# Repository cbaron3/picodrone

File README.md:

# picodrone

Micro drone project using STM32

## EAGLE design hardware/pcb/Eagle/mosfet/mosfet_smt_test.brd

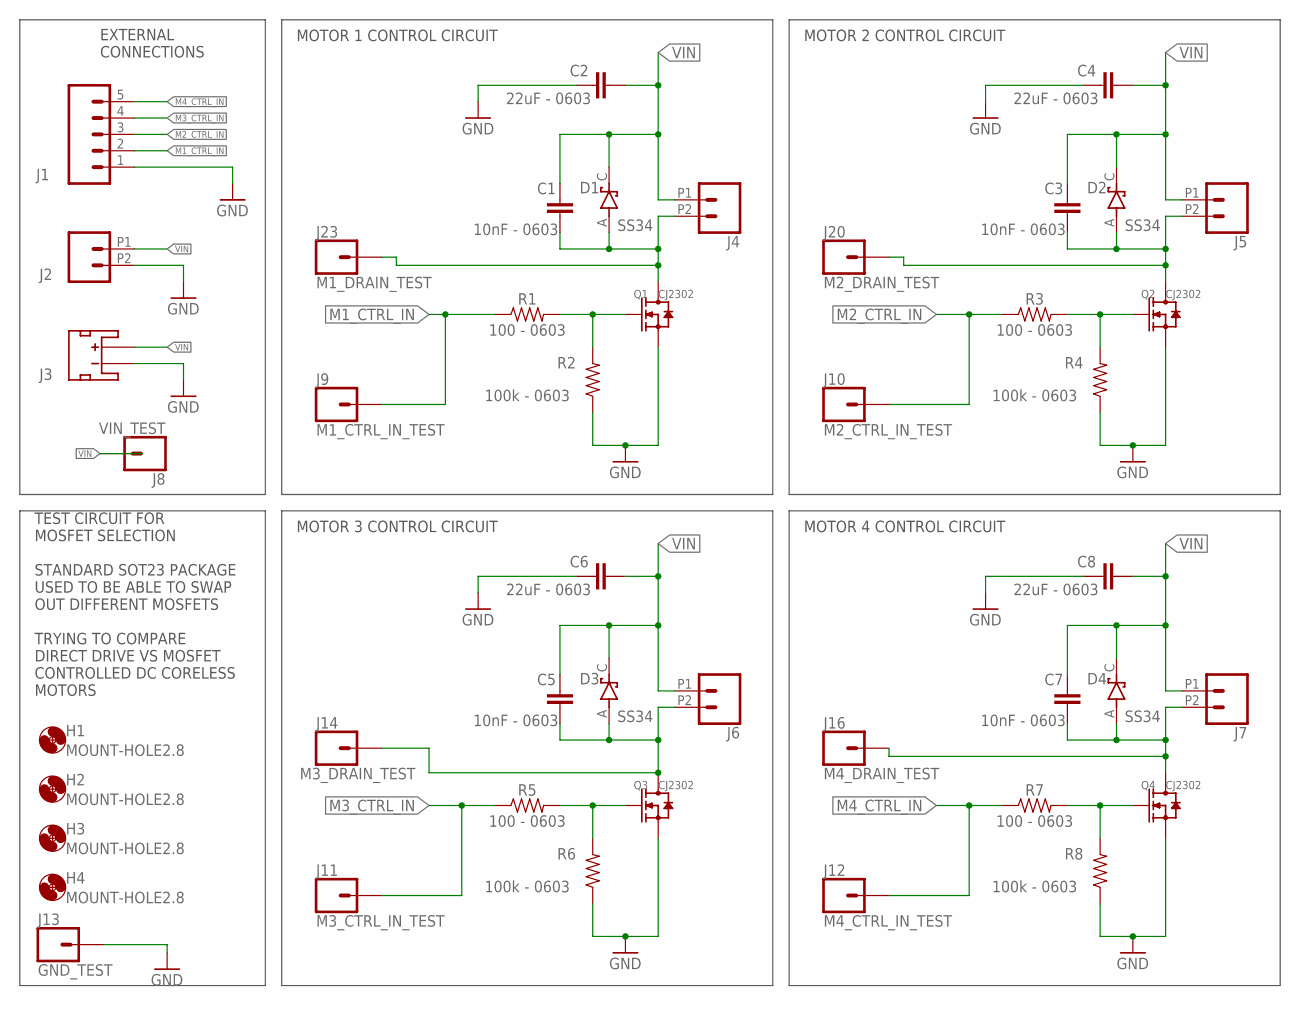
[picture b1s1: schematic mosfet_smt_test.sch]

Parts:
C1, C3, C5, C7: 10nF - 0603; CAP_0603
C2, C4, C6, C8: 22uF - 0603; CAP_0603
D1, D2, D3, D4: SS34; DIOM7959X265N
H1, H2, H3, H4: MOUNT-HOLE2.8; 2,8
J1: CONN_05; 1X05
J2, J4, J5, J6, J7: CONN_022.54MM_SCREWTERM; 1X02_2.54_SCREWTERM
J3: JST_2MM_MALE; JST-2-SMD
J8: VIN_TEST; 1X01
J9: M1_CTRL_IN_TEST; 1X01
J10: M2_CTRL_IN_TEST; 1X01
J11: M3_CTRL_IN_TEST; 1X01
J12: M4_CTRL_IN_TEST; 1X01
J13: GND_TEST; 1X01
J14: M3_DRAIN_TEST; 1X01
J16: M4_DRAIN_TEST; 1X01
J20: M2_DRAIN_TEST; 1X01
J23: M1_DRAIN_TEST; 1X01
Q1, Q2, Q3, Q4: CJ2302; SOT-23
R1, R3, R5, R7: 100 - 0603; 0603
R2, R4, R6, R8: 100k - 0603; 0603

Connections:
GND: C2.2, C4.2, C6.2, C8.2, J1.1, J2.P2 (2), J3.1 (-), J13.1, Q1.2 (S), Q2.2 (S), Q3.2 (S), Q4.2 (S), R2.1, R4.1, R6.1, R8.1
M1_CTRL_IN: J1.2, J9.1, R1.1
M2_CTRL_IN: J1.3, J10.1, R3.1
M3_CTRL_IN: J1.4, J11.1, R5.1
M4_CTRL_IN: J1.5, J12.1, R7.1
unnamed: Q1.1 (G), R1.2, R2.2
unnamed: C1.2, D1.A, J4.P2 (2), J23.1, Q1.3 (D)
unnamed: Q2.1 (G), R3.2, R4.2
unnamed: C3.2, D2.A, J5.P2 (2), J20.1, Q2.3 (D)
unnamed: Q3.1 (G), R5.2, R6.2
unnamed: C5.2, D3.A, J6.P2 (2), J14.1, Q3.3 (D)
unnamed: Q4.1 (G), R7.2, R8.2
unnamed: C7.2, D4.A, J7.P2 (2), J16.1, Q4.3 (D)
VIN: C1.1, C2.1, C3.1, C4.1, C5.1, C6.1, C7.1, C8.1, D1.C (K), D2.C (K), D3.C (K), D4.C (K), J2.P1 (1), J3.2 (+), J4.P1 (1), J5.P1 (1), J6.P1 (1), J7.P1 (1), J8.1

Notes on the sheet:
MOTOR 1 CONTROL CIRCUIT
MOTOR 2 CONTROL CIRCUIT
MOTOR 3 CONTROL CIRCUIT
MOTOR 4 CONTROL CIRCUIT
EXTERNAL CONNECTIONS
TEST CIRCUIT FOR MOSFET SELECTION STANDARD SOT23 PACKAGE USED TO BE ABLE TO SWAP OUT DIFFERENT MOSFETS TRYING TO COMPARE DIRECT DRIVE VS MOSFET CONTROLLED DC CORELESS MOTORS

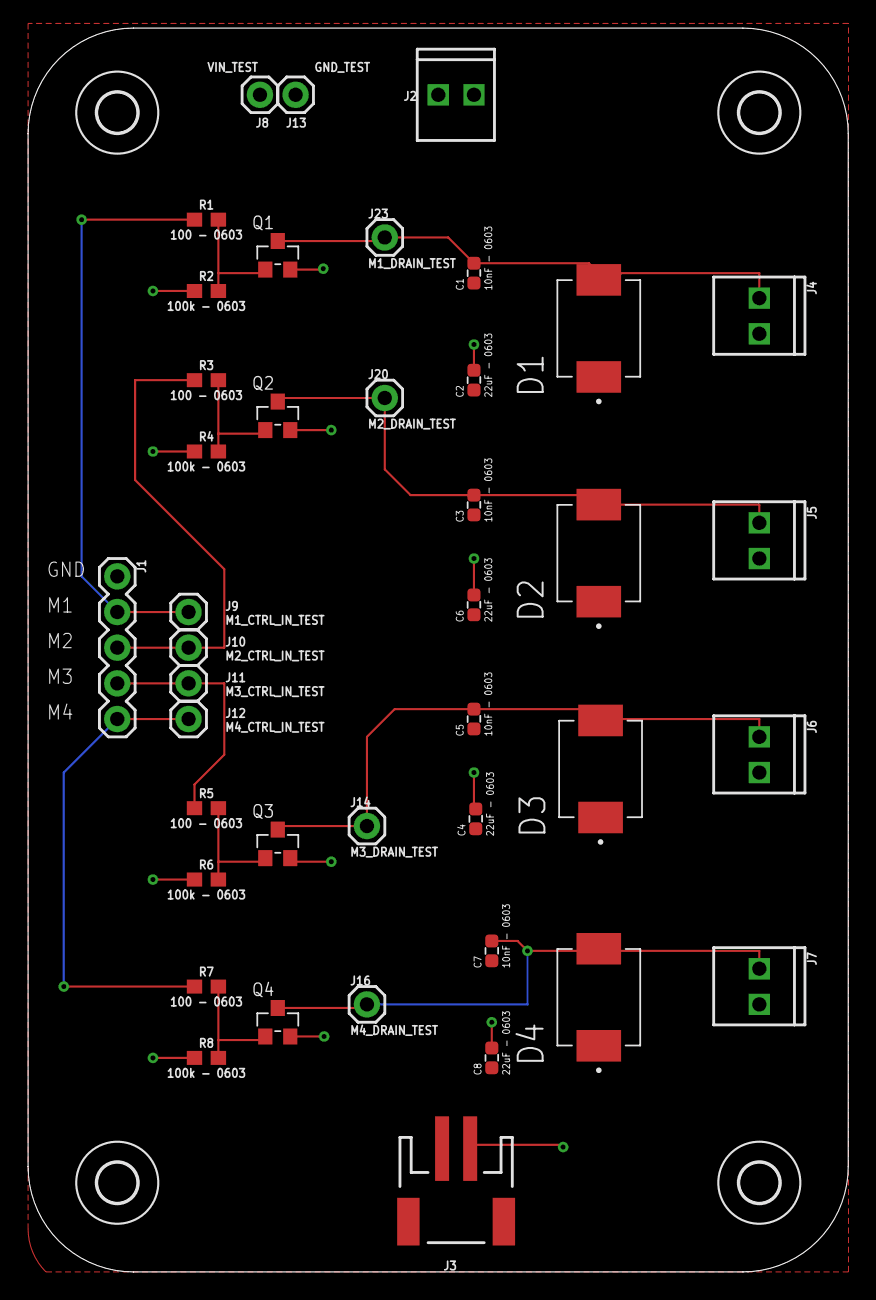
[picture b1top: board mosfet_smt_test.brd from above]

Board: 2 copper layers, 58.4 x 88.6 mm, 45 parts (0 on the bottom side), 14 nets.

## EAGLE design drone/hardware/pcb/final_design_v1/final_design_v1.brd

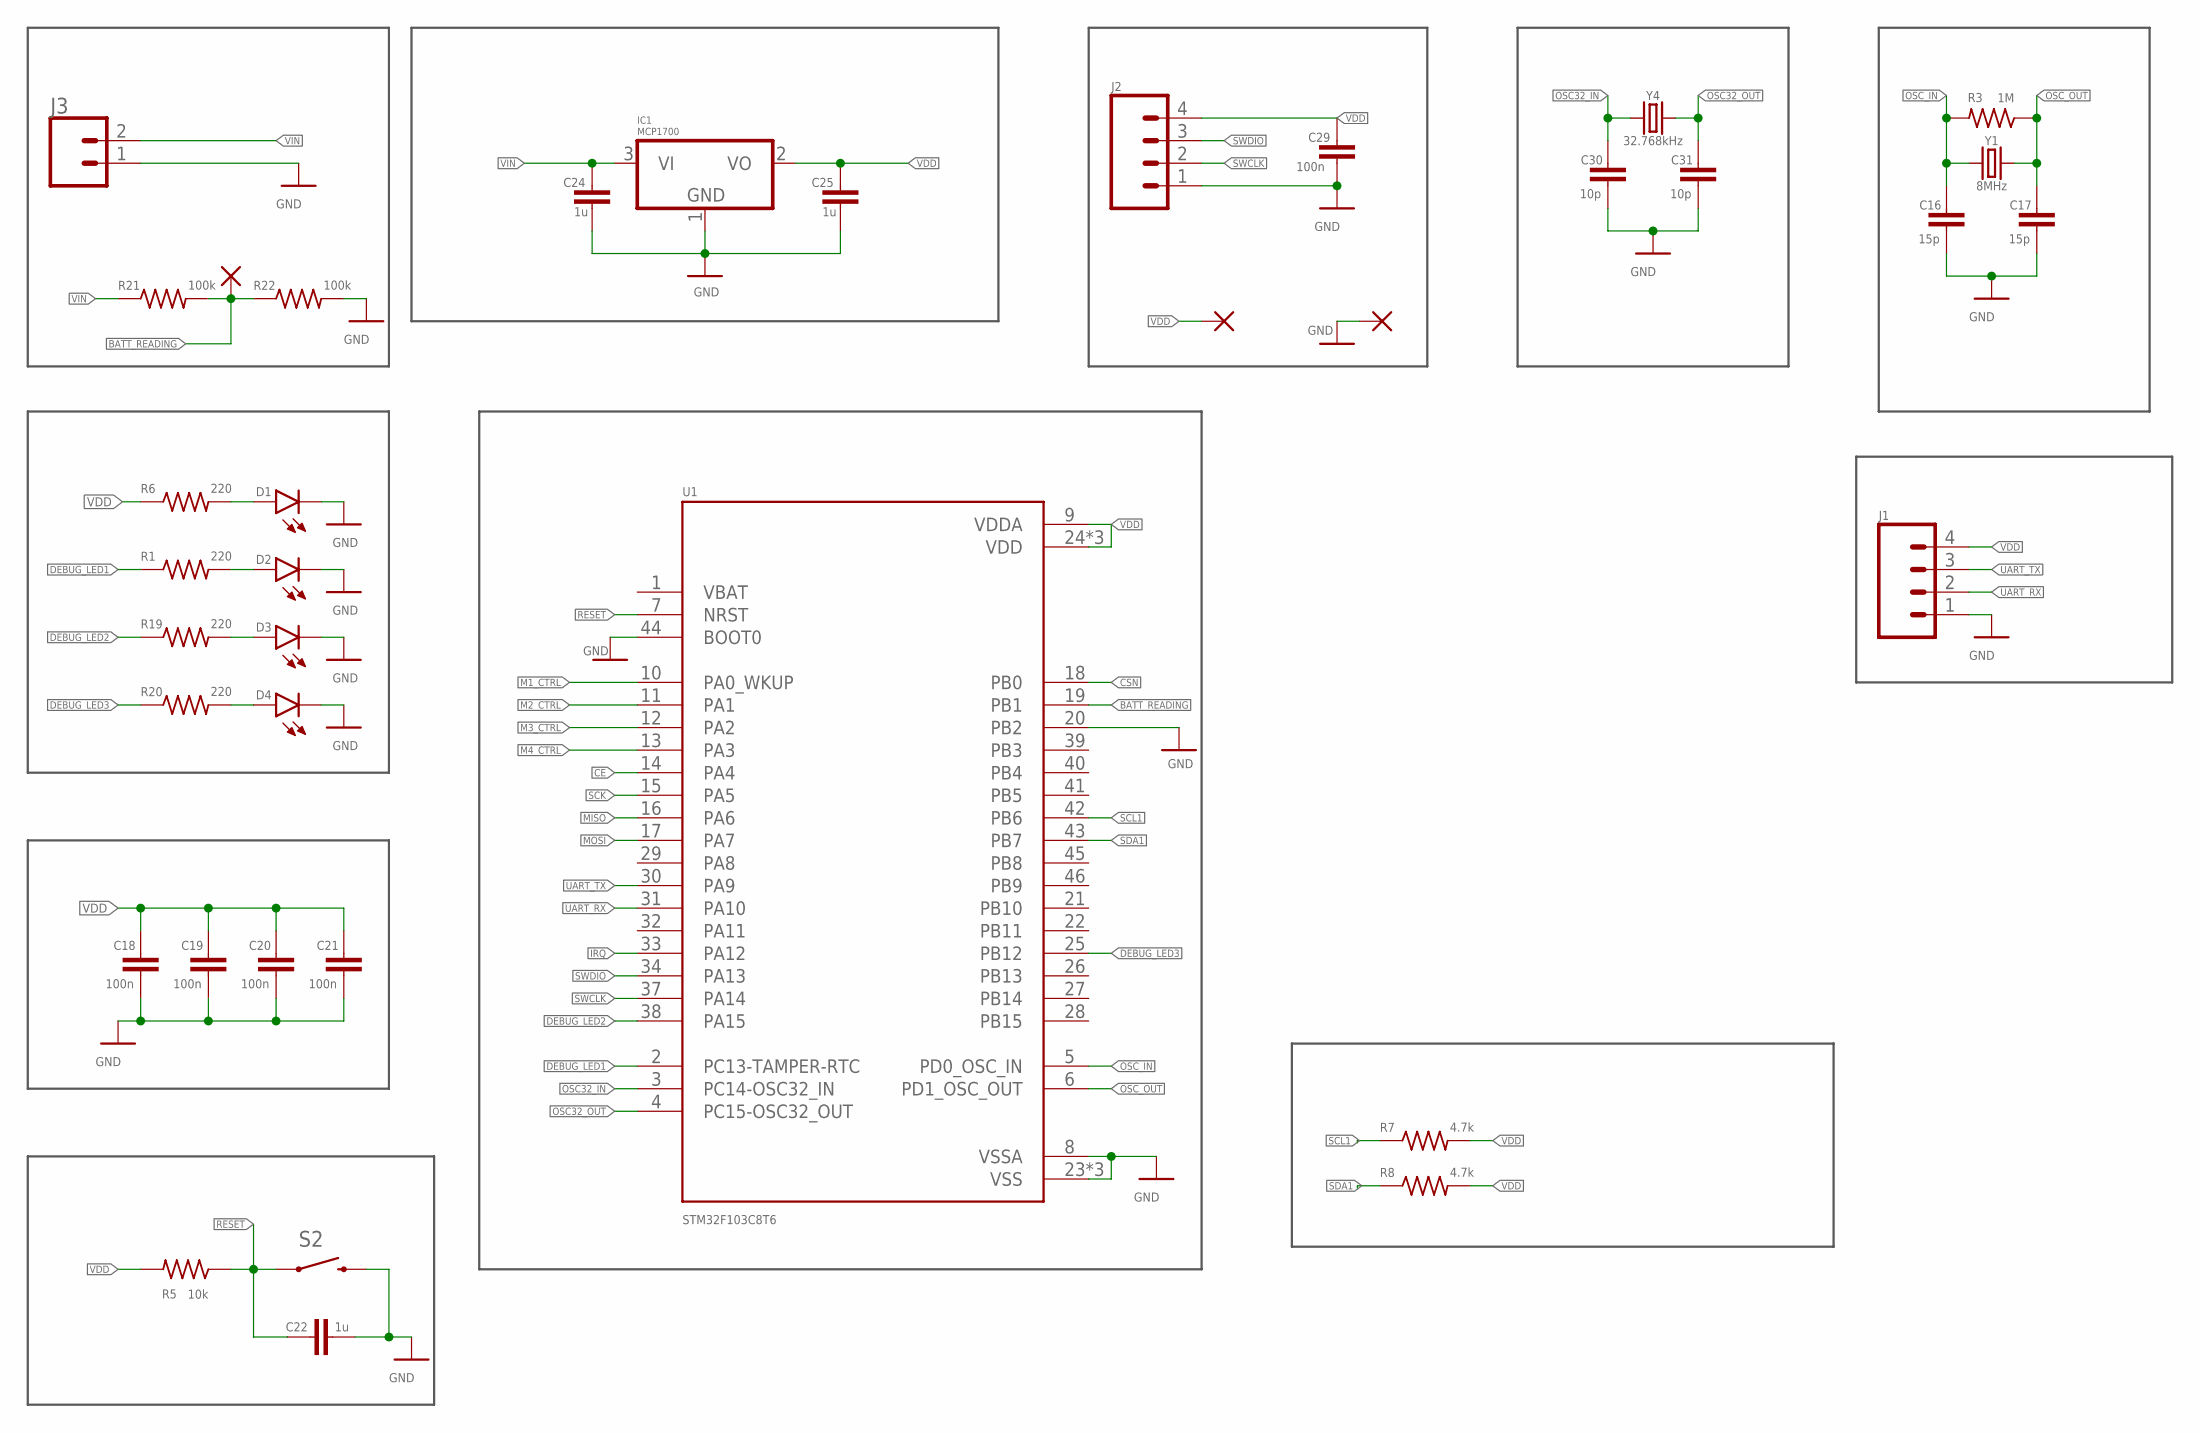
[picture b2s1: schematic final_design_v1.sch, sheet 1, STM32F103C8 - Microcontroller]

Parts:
+M18, +M19, +M20: SMD2; SMD1,27-2,54
C16, C17: 15p; CAP_0603
C18, C19, C20, C21, C29: 100n; CAP_0603
C22, C24, C25: 1u; CAP_0603
C30, C31: 10p; CAP_0603
D1, D2, D3, D4: LED0603; LED-0603
IC1: MCP1700; SOT23
J1, J2: CONN_04; 1X04
J3: CONN_02; 1X02
R1, R6, R19, R20: 220; RES_0603
R3: 1M; RES_0603
R5: 10k; RES_0603
R7, R8: 4.7k; RES_0603
R21, R22: 100k; RES_0603
S2: RS032G05A3SM-SPST-MOMENTARY-SWSMD-1101NE; TACTILE-SWITCH-1101NE
U1: STM32F103C8T6; QFP50P900X900X160-48N
Y1: 8MHz; CRYSTAL-SMD-5X3.2-4PAD
Y4: 32.768kHz; CRYSTAL-SMD-3.2X1.5MM

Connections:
BATT_READING: +M20.1, R21.2, R22.1, U1.19 (PB1)
CE: U1.14 (PA4); also elsewhere on the board
CSN: U1.18 (PB0); also elsewhere on the board
DEBUG_LED1: R1.1, U1.2 (PC13-TAMPER-RTC)
DEBUG_LED2: R19.1, U1.38 (PA15)
DEBUG_LED3: R20.1, U1.25 (PB12)
GND: +M19.1, C16.2, C17.2, C18.2, C19.2, C20.2, C21.2, C22.2, C24.2, C25.2, C29.2, C30.2, C31.2, D1.C, D2.C, D3.C, D4.C, IC1.1 (GND), J1.1, J2.1, J3.1, R22.2, S2.2, U1.8 (VSSA), U1.20 (PB2), U1.23 (VSS), U1.35 (VSS), U1.44 (BOOT0), U1.47 (VSS); also elsewhere on the board
IRQ: U1.33 (PA12); also elsewhere on the board
M1_CTRL: U1.10 (PA0_WKUP); also elsewhere on the board
M2_CTRL: U1.11 (PA1); also elsewhere on the board
M3_CTRL: U1.12 (PA2); also elsewhere on the board
M4_CTRL: U1.13 (PA3); also elsewhere on the board
MISO: U1.16 (PA6); also elsewhere on the board
MOSI: U1.17 (PA7); also elsewhere on the board
unnamed: D1.A, R6.2
unnamed: D2.A, R1.2
unnamed: D3.A, R19.2
unnamed: D4.A, R20.2
OSC32_IN: C30.1, U1.3 (PC14-OSC32_IN), Y4.P$1 (1)
OSC32_OUT: C31.1, U1.4 (PC15-OSC32_OUT), Y4.P$2 (2)
OSC_IN: C16.1, R3.2, U1.5 (PD0_OSC_IN), Y1.1
OSC_OUT: C17.1, R3.1, U1.6 (PD1_OSC_OUT), Y1.3 (2)
RESET: C22.1, R5.1, S2.1, U1.7 (NRST)
SCK: U1.15 (PA5); also elsewhere on the board
SCL1: R7.1, U1.42 (PB6); also elsewhere on the board
SDA1: R8.1, U1.43 (PB7); also elsewhere on the board
SWCLK: J2.2, U1.37 (PA14)
SWDIO: J2.3, U1.34 (PA13)
UART_RX: J1.2, U1.31 (PA10)
UART_TX: J1.3, U1.30 (PA9)
VDD: +M18.1, C18.1, C19.1, C20.1, C21.1, C25.1, C29.1, IC1.2 (VO), J1.4, J2.4, R5.2, R6.1, R7.2, R8.2, U1.9 (VDDA), U1.24 (VDD), U1.36 (VDD), U1.48 (VDD); also elsewhere on the board
VIN: C24.1, IC1.3 (VI), J3.2, R21.1; also elsewhere on the board

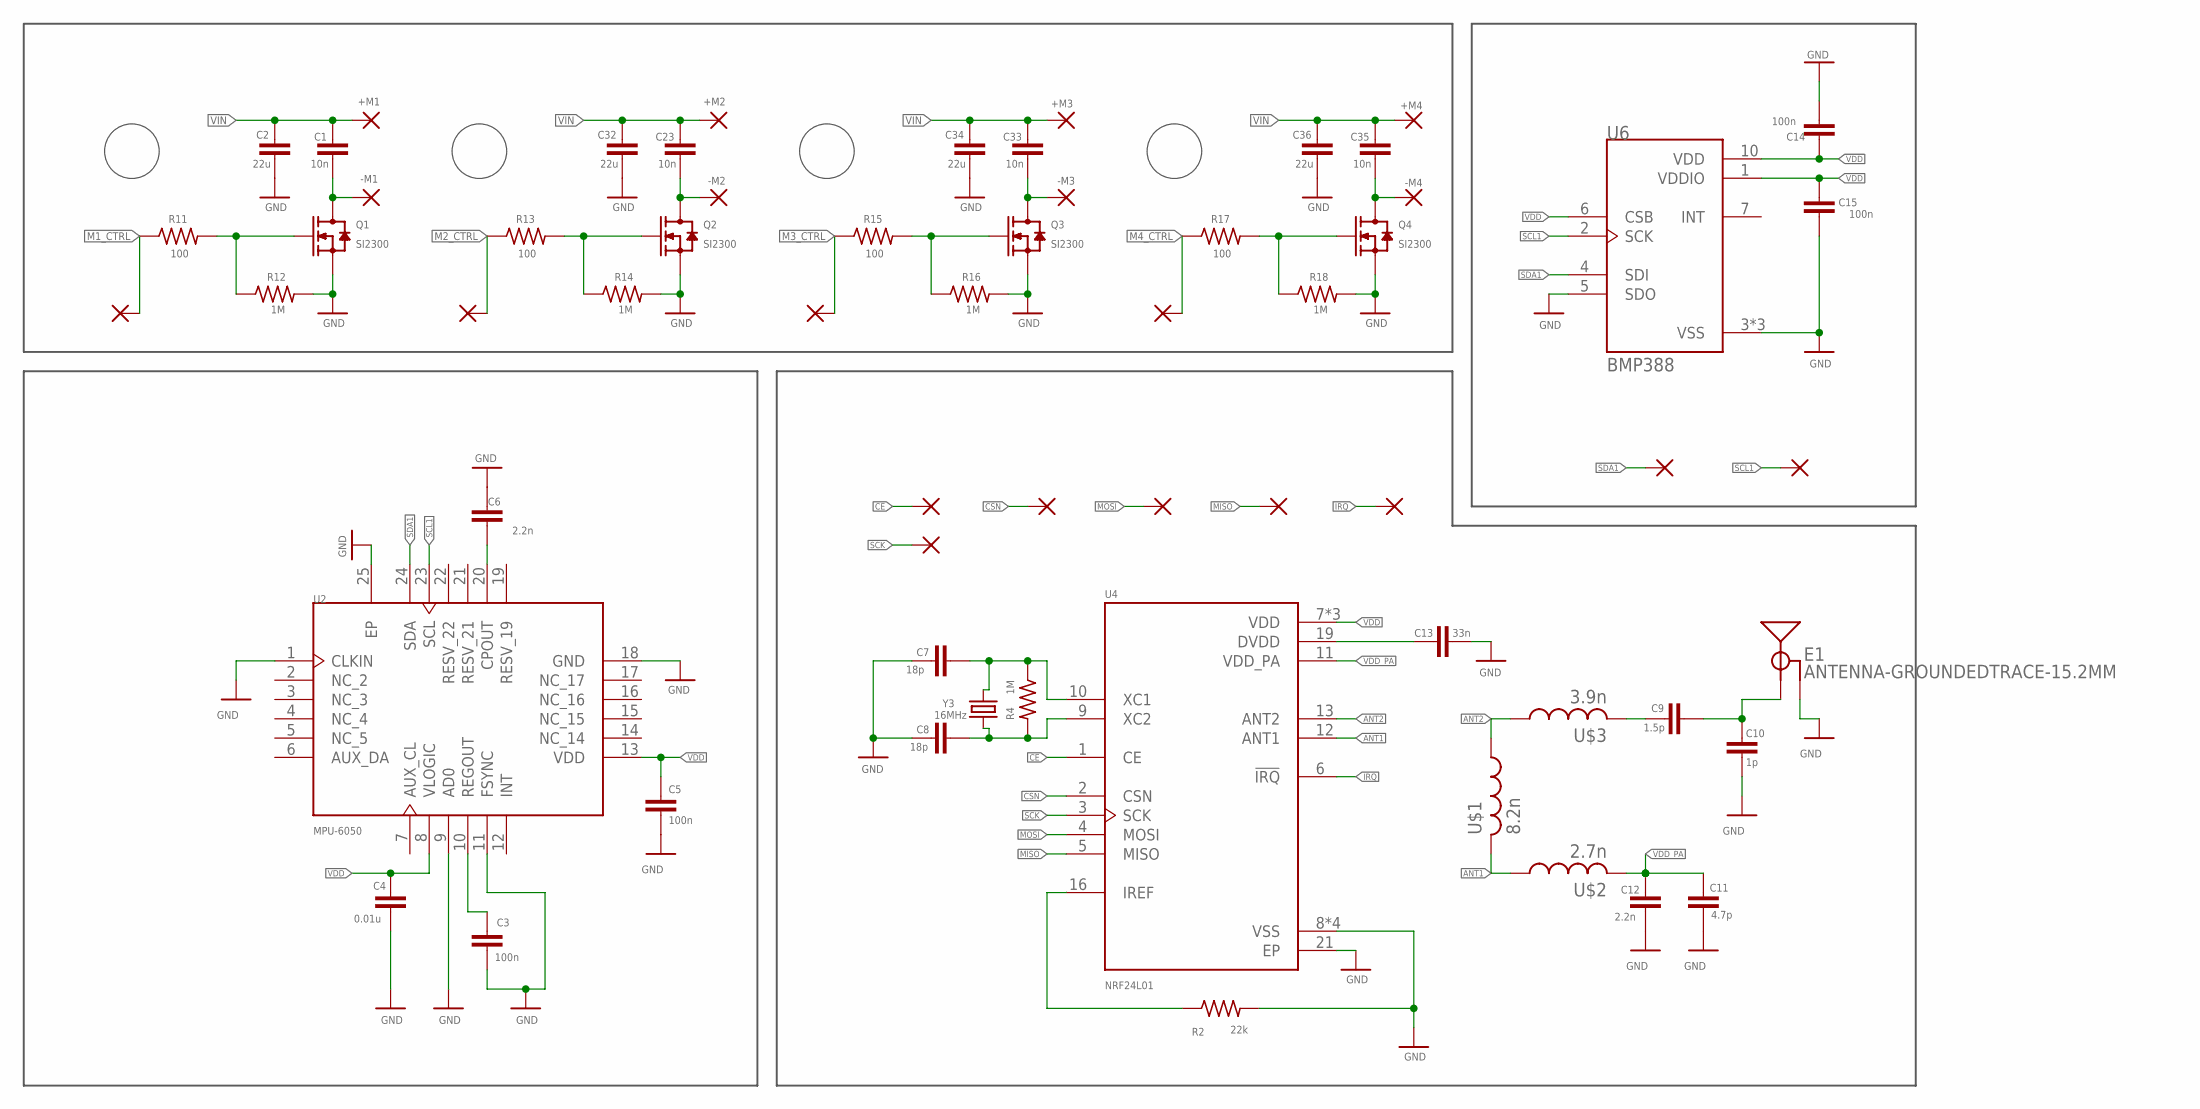
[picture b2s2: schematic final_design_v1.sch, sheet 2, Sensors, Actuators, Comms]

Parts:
+M1, +M2, +M3, +M4, +M5, +M6, +M7, +M8, +M9, +M10, +M13, +M14, +M15, +M16, +M17, +M22: SMD2; SMD1,27-2,54
-M1, -M2, -M3, -M4: SMD2; SMD1,27-2,54
C1, C23, C33, C35: 10n; CAP_0603
C2, C32, C34, C36: 22u; CAP_0603
C3, C5, C14, C15: 100n; CAP_0603
C4: 0.01u; CAP_0603
C6, C12: 2.2n; CAP_0603
C7, C8: 18p; CAP_0603
C9: 1.5p; CAP_0603
C10: 1p; CAP_0603
C11: 4.7p; CAP_0603
C13: 33n; CAP_0603
E1: ANTENNA-GROUNDEDTRACE-15.2MM; TRACE_ANTENNA_2.4GHZ_15.2MM
Q1, Q2, Q3, Q4: SI2300; SOT-23
R2: 22k; RES_0603
R4, R12, R14, R16, R18: 1M; RES_0603
R11, R13, R15, R17: 100; RES_0603
U2: MPU-6050; 24-VFQFN
U4: NRF24L01; QFN50P400X400X95-21N
U6: BMP388; PQFN50P200X200X80-10N
U$1: 8.2n; RESC0603_N
U$2: 2.7n; RESC0603_N
U$3: 3.9n; RESC0603_N
Y3: 16MHz; CRYSTAL-SMD-5X3.2-4PAD

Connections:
ANT1: U4.12 (ANT1), U$1.2, U$2.1
ANT2: U4.13 (ANT2), U$1.1, U$3.1
CE: +M13.1, U4.1 (CE); also elsewhere on the board
CSN: +M14.1, U4.2 (CSN); also elsewhere on the board
GND: C2.1, C3.2, C4.2, C5.2, C6.2, C7.2, C8.2, C10.1, C11.1, C12.1, C13.2, C14.2, C15.1, C32.1, C34.1, C36.1, E1.GND, Q1.2 (S), Q2.2 (S), Q3.2 (S), Q4.2 (S), R2.2, R12.2, R14.2, R16.2, R18.2, U2.1 (CLKIN), U2.9 (AD0), U2.11 (FSYNC), U2.18 (GND), U2.25 (EP), U4.8 (VSS), U4.14 (VSS), U4.17 (VSS), U4.20 (VSS), U4.21 (EP), U6.3 (VSS), U6.5 (SDO), U6.8 (VSS), U6.9 (VSS); also elsewhere on the board
IRQ: +M17.1, U4.6 (!IRQ); also elsewhere on the board
M1_CTRL: +M10.1, R11.1; also elsewhere on the board
M2_CTRL: +M9.1, R13.1; also elsewhere on the board
M3_CTRL: +M8.1, R15.1; also elsewhere on the board
M4_CTRL: +M7.1, R17.1; also elsewhere on the board
MISO: +M16.1, U4.5 (MISO); also elsewhere on the board
MOSI: +M15.1, U4.4 (MOSI); also elsewhere on the board
unnamed: -M1.1, C1.1, Q1.3 (D)
unnamed: C3.1, U2.10 (REGOUT)
unnamed: C6.1, U2.20 (CPOUT)
unnamed: C8.1, R4.2, U4.9 (XC2), Y3.1
unnamed: C7.1, R4.1, U4.10 (XC1), Y3.3 (2)
unnamed: R2.1, U4.16 (IREF)
unnamed: -M2.1, C23.1, Q2.3 (D)
unnamed: Q1.1 (G), R11.2, R12.1
unnamed: C9.2, C10.2, E1.ANT (SIGNAL)
unnamed: C9.1, U$3.2
unnamed: Q2.1 (G), R13.2, R14.1
unnamed: -M3.1, C33.1, Q3.3 (D)
unnamed: Q3.1 (G), R15.2, R16.1
unnamed: C13.1, U4.19 (DVDD)
unnamed: -M4.1, C35.1, Q4.3 (D)
unnamed: Q4.1 (G), R17.2, R18.1
SCK: +M22.1, U4.3 (SCK); also elsewhere on the board
SCL1: +M6.1, U2.23 (SCL), U6.2 (SCK); also elsewhere on the board
SDA1: +M5.1, U2.24 (SDA), U6.4 (SDI); also elsewhere on the board
VDD: C4.1, C5.1, C14.1, C15.2, U2.8 (VLOGIC), U2.13 (VDD), U4.7 (VDD), U4.15 (VDD), U4.18 (VDD), U6.1 (VDDIO), U6.6 (CSB), U6.10 (VDD); also elsewhere on the board
VDD_PA: C11.2, C12.2, U4.11 (VDD_PA), U$2.2
VIN: +M1.1, +M2.1, +M3.1, +M4.1, C1.2, C2.2, C23.2, C32.2, C33.2, C34.2, C35.2, C36.2; also elsewhere on the board

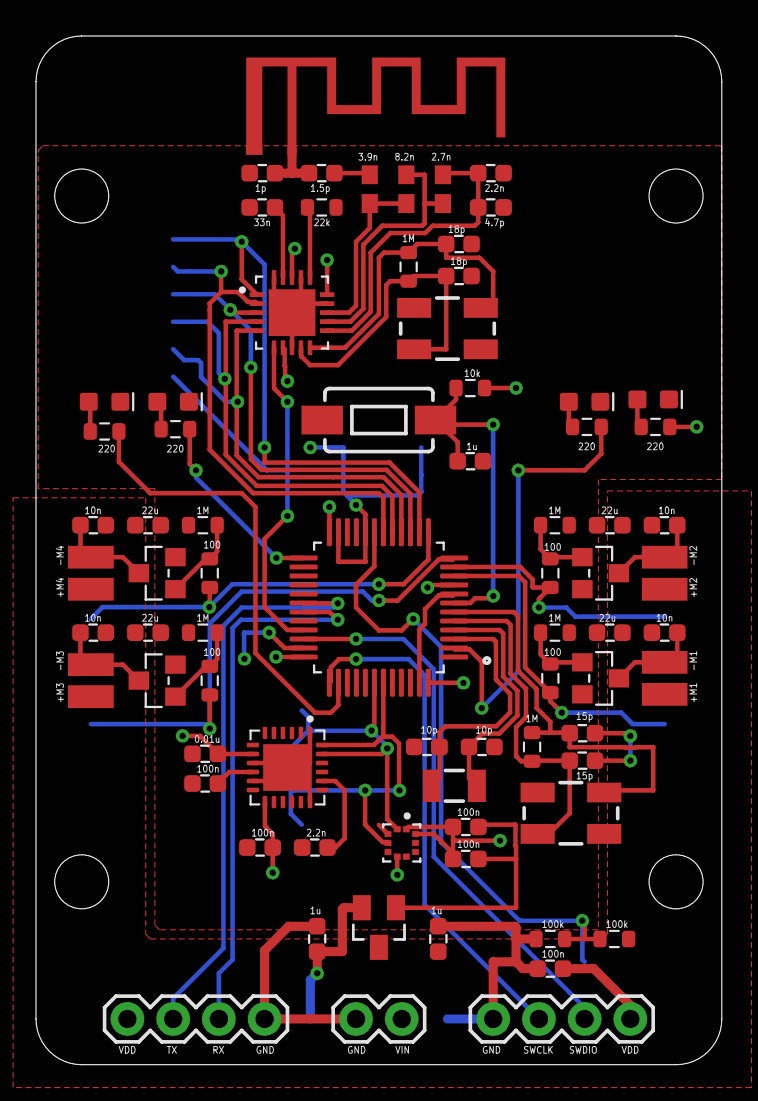
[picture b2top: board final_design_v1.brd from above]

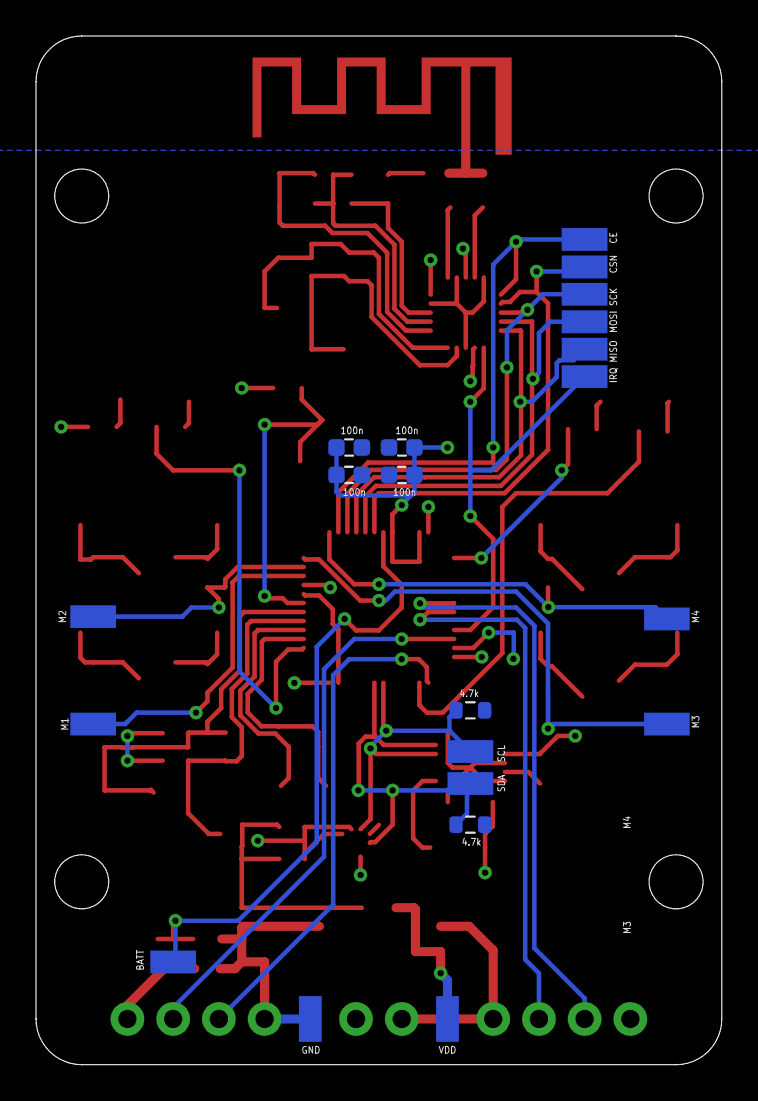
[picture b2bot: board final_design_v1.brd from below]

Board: 2 copper layers, 38.1 x 57.1 mm, 100 parts (21 on the bottom side), 51 nets.

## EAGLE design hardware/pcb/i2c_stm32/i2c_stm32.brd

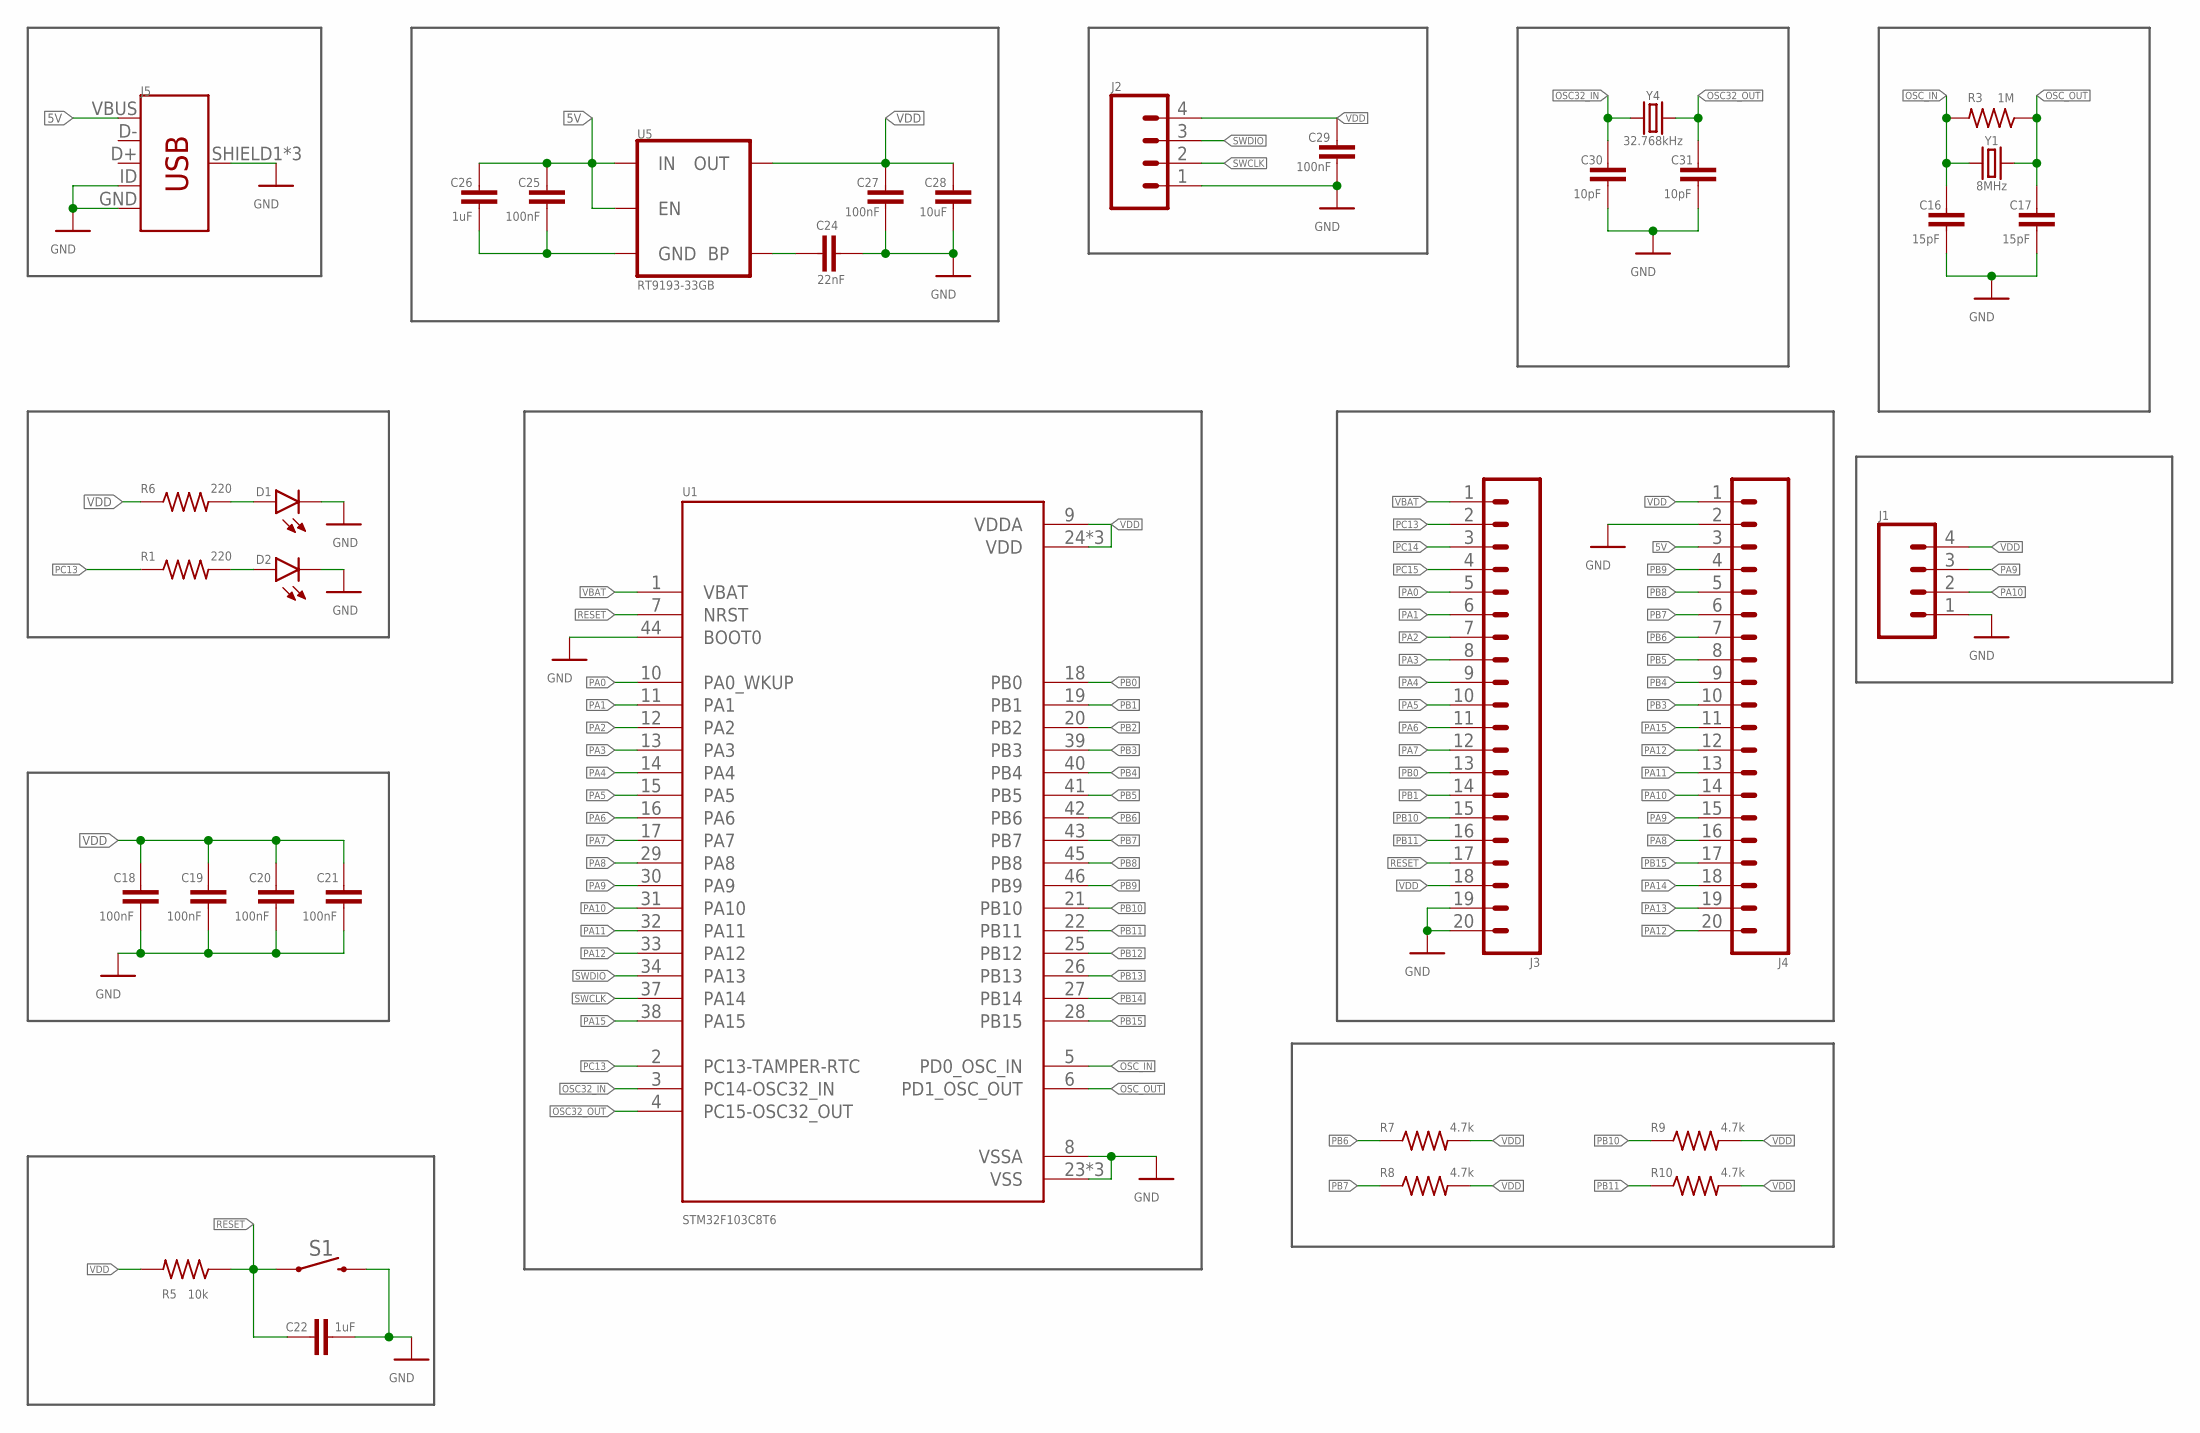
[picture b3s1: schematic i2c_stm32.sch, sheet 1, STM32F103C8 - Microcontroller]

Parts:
C16, C17: 15pF; CAP_0603
C18, C19, C20, C21, C25, C27, C29: 100nF; CAP_0603
C22, C26: 1uF; CAP_0603
C24: 22nF; CAP_0603
C28: 10uF; CAP_0603
C30, C31: 10pF; CAP_0603
D1, D2: LED0603; LED-0603
J1, J2: CONN_04; 1X04
J3, J4: CONN_20; 1X20
J5: USB_MICRO-B_FEMALE-SMT; USB-B-MICRO-SMD
R1, R6: 220; RES_0603
R3: 1M; RES_0603
R5: 10k; RES_0603
R7, R8, R9, R10: 4.7k; RES_0603
S1: MOMENTARY-SWITCH-SPST-PTH-6.0MM; TACTILE_SWITCH_PTH_6.0MM
U1: STM32F103C8T6; QFP50P900X900X160-48N
U5: RT9193-33GB; SOT23-5
Y1: 8MHz; CRYSTAL-SMD-5X3.2-4PAD
Y4: 32.768kHz; CRYSTAL-SMD-3.2X1.5MM

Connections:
5V: C25.2, C26.2, J4.3, J5.VBUS, U5.1 (IN), U5.3 (EN)
GND: C16.2, C17.2, C18.2, C19.2, C20.2, C21.2, C22.2, C24.1, C27.2, C28.2, C29.2, C30.2, C31.2, D1.C, D2.C, J1.1, J2.1, J3.19, J3.20, J4.2, J5.GND, J5.ID, J5.SHIELD1 (SHIELD), J5.SHIELD2 (SHIELD), J5.SHIELD3 (SHIELD), S1.3 (2), U1.8 (VSSA), U1.23 (VSS), U1.35 (VSS), U1.44 (BOOT0), U1.47 (VSS); also elsewhere on the board
unnamed: D1.A, R6.2
unnamed: C24.2, U5.4 (BP)
unnamed: D2.A, R1.2
unnamed: C25.1, C26.1, U5.2 (GND)
OSC32_IN: C30.1, U1.3 (PC14-OSC32_IN), Y4.P$1 (1)
OSC32_OUT: C31.1, U1.4 (PC15-OSC32_OUT), Y4.P$2 (2)
OSC_IN: C16.1, R3.2, U1.5 (PD0_OSC_IN), Y1.1
OSC_OUT: C17.1, R3.1, U1.6 (PD1_OSC_OUT), Y1.3 (2)
PA0: J3.5, U1.10 (PA0_WKUP)
PA1: J3.6, U1.11 (PA1); also elsewhere on the board
PA2: J3.7, U1.12 (PA2)
PA3: J3.8, U1.13 (PA3)
PA4: J3.9, U1.14 (PA4); also elsewhere on the board
PA5: J3.10, U1.15 (PA5); also elsewhere on the board
PA6: J3.11, U1.16 (PA6); also elsewhere on the board
PA7: J3.12, U1.17 (PA7); also elsewhere on the board
PA8: J4.16, U1.29 (PA8)
PA9: J1.3, J4.15, U1.30 (PA9)
PA10: J1.2, J4.14, U1.31 (PA10)
PA11: J4.13, U1.32 (PA11)
PA12: J4.12, J4.20, U1.33 (PA12)
PA13: J4.19
PA14: J4.18
PA15: J4.11, U1.38 (PA15)
PB0: J3.13, U1.18 (PB0); also elsewhere on the board
PB1: J3.14, U1.19 (PB1); also elsewhere on the board
PB2: U1.20 (PB2)
PB3: J4.10, U1.39 (PB3)
PB4: J4.9, U1.40 (PB4)
PB5: J4.8, U1.41 (PB5)
PB6: J4.7, R7.1, U1.42 (PB6); also elsewhere on the board
PB7: J4.6, R8.1, U1.43 (PB7); also elsewhere on the board
PB8: J4.5, U1.45 (PB8)
PB9: J4.4, U1.46 (PB9); also elsewhere on the board
PB10: J3.15, R9.1, U1.21 (PB10); also elsewhere on the board
PB11: J3.16, R10.1, U1.22 (PB11); also elsewhere on the board
PB12: U1.25 (PB12)
PB13: U1.26 (PB13)
PB14: U1.27 (PB14)
PB15: J4.17, U1.28 (PB15)
PC13: J3.2, R1.1, U1.2 (PC13-TAMPER-RTC)
PC14: J3.3
PC15: J3.4
RESET: C22.1, J3.17, R5.1, S1.1, U1.7 (NRST)
SWCLK: J2.2, U1.37 (PA14)
SWDIO: J2.3, U1.34 (PA13)
VBAT: J3.1, U1.1 (VBAT)
VDD: C18.1, C19.1, C20.1, C21.1, C27.1, C28.1, C29.1, J1.4, J2.4, J3.18, J4.1, R5.2, R6.1, R7.2, R8.2, R9.2, R10.2, U1.9 (VDDA), U1.24 (VDD), U1.36 (VDD), U1.48 (VDD), U5.5 (OUT); also elsewhere on the board

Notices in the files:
parts and their libraries:
SparkFun-LED: Licensing: Creative Commons ShareAlike 4.0 International - https://creativecommons.org/licenses/by-sa/4.0
